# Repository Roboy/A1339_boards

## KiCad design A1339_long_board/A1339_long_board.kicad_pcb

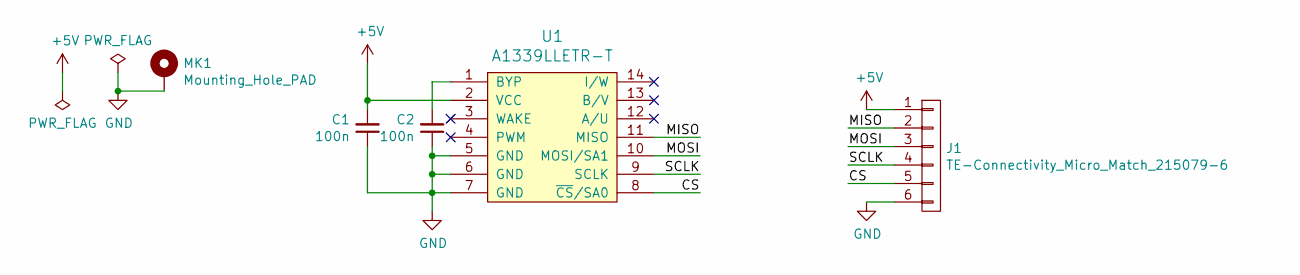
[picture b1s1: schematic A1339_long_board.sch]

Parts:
C1, C2: 100n; The_0402_FP
J1: TE-Connectivity_Micro_Match_215079-6; TE-Connectivity_Micro-Match_connector_02x03_Pitch_1.27mm
MK1: Mounting_Hole_PAD; MountingHole_2.2mm_M2_DIN965_Pad
U1: A1339LLETR-T; TSSOP-14_4.4x5mm_P0.65mm

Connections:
+5V: C1.2, J1.1, U1.2 (VCC)
/CS: J1.5, U1.8 (~CS~/SA0)
/MISO: J1.2, U1.11 (MISO)
/MOSI: J1.3, U1.10 (MOSI/SA1)
/SCLK: J1.4, U1.9 (SCLK)
GND: C1.1, C2.1, J1.6, MK1.1, U1.5 (GND), U1.6 (GND), U1.7 (GND)
unnamed: C2.2, U1.1 (BYP)

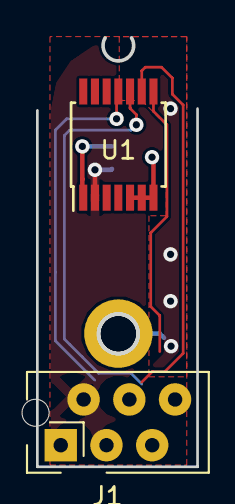
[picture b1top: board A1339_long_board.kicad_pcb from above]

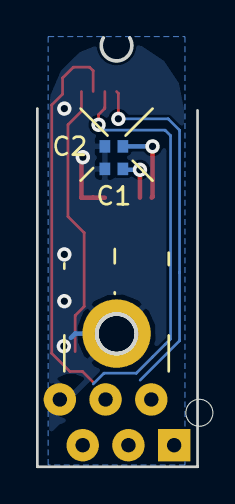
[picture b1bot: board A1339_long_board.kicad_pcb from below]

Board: 2 copper layers, 8.9 x 23.8 mm, 5 parts (2 on the bottom side), 7 nets.

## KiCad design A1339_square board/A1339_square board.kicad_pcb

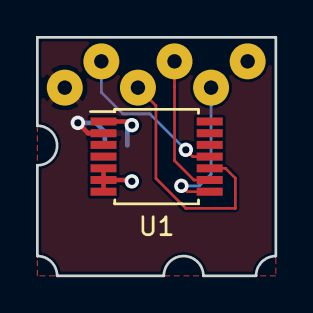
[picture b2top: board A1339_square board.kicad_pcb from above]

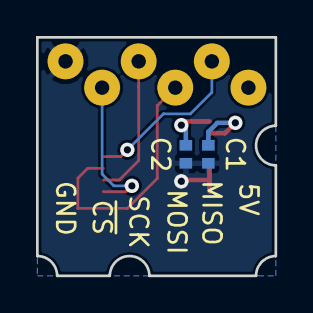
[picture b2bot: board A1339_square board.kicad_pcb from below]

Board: 2 copper layers, 13.2 x 13.2 mm, 8 parts (2 on the bottom side), 6 nets.

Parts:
5V: Test_Point; SolderWirePad_single_0-8mmDrill
C1, C2: 100n; The_0402_FP
GND: Test_Point; SolderWirePad_single_0-8mmDrill
MISO: Test_Point; SolderWirePad_single_0-8mmDrill
MOSI: Test_Point; SolderWirePad_single_0-8mmDrill
SCK: Test_Point; SolderWirePad_single_0-8mmDrill
U1: A1339LLETR-T; TSSOP-14_4.4x5mm_P0.65mm

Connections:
+5V: 5V.1, C1.2, U1.2
/MISO: MISO.1, U1.11
/MOSI: MOSI.1, U1.10
/SCLK: SCK.1, U1.9
GND: C1.1, C2.1, GND.1, U1.5, U1.6, U1.7
unnamed: C2.2, U1.1

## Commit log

2018-11-19 Boards done so quick, they are already manufactured on the first commit ¯\_(ツ)_/¯
2019-01-22 Chmodded all files properly. Damn windows filesystems -.-
2019-02-27 draft
